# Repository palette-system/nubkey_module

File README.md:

# nubkey_module
Nubkey をPIM447と同じ通信で使用できるようにしたモジュールです。

<br><br>

<table>
<tr><td></td><td></td></tr>
</table>

<br><br>

## ドキュメント

<a href="/docs/structure.md">nubkey_module　基礎知識</a><br>
nubkey_modul を使用するにあたり作成者も、設計者も一度確認してからご使用ください。<br>
<br>

<a href="/docs/module_build.md">nubkey_module　はんだ付け手順</a><br>
nubkey_module をPCBにはんだ付けする際にご確認下さい。<br>
<br>

<a href="/docs/tester_build.md">nubkey_module tester　ビルドガイド</a><br>
nubkey_module tester を組み立てる際にご確認下さい。<br>
<br>

<a href="https://palette-system.github.io/nubkey_module/">nubkey_module tester　ファームウェア書き込み</a><br>
nubkey_module tester を使用する際にご確認下さい。<br>
<br>

<a href="/docs/command.md">nubkey_module　通信仕様</a><br>
nubkey_module で実行できるI2Cのコマンドの仕様書です。QMK等から速度調節する場合等にご確認下さい。<br>
<br>

<a href="/hardware/nubkey_module_tester/">nubkey_module tester　KiCadデータ</a><br>
nubkey_module tester のKiCadデータです。nubkey_module を使用したキーボードを作る際の参考にして下さい。<br>
<br>
<br>

## 基本的な接続
<br>
<br>
<br>

## キャリブレーション
どんなに気を付けて作成しても組み立て毎に磁気スイッチの中心位置が0.数ミリズレが生じます。<br>
キャリブレーションスイッチを押したまま、Nubkeyを押下して上下左右にグリグリ動かす事で nubkey_module のソフト側で中心位置を調節できます。<br>
<br>

## オススメの構造
<br>
<br>
<br>

<br>
<br>

## ピンの説明

|  ピン  |  説明  |
|  ----  |  :---  |
|  UPDI  |  nubkey_module のファームを更新するためのピンです  |
|  addr 0x0B  |  nubkey_module のI2Cアドレスを0x0Bにするピンです。<br>このピンをGNDに接続した状態で起動するとI2Cアドレスが0x0Bになります。  |
|  raw res  |  I2CのレスポンスがデフォルトではPIM447互換ですがこのピンをGNDに接続すると「short X座標, short Y座標, short スイッチの押し込み具合」を返すようになります。  |
|  actuation  |  アクチュエーションポイント設定ピンです。このピンをGNDに接続するとアクチュエーション設定モードに入ります。その後GNDへの接続を切断したタイミングのKS-20のスイッチの高さがアクチュエーションポイントとしてnubkey_moduleに保存されます。  |
|  nubkey off  |  このピンをGNDに接続すると、マウス移動が無しの状態になりスイッチのON/OFFのみが変わるようになります。この時actuationピンで設定したスイッチの高さでON/OFFが切り替わります。  |
|  GND  |  GNDです  |
|  VCC  |  電源です。3.3Vを接続して下さい。  |
|  SCL  |  I2C通信用（SCL）  |
|  SDA  |  I2C通信用（SDA）  |
|  calibration  |  キャリブレーションピンです。このピンをGNDに接続した状態でKS-20のスイッチを押してグリグリすると、Nubkeyの中心位置を調節できます。<br>キャリブレーションの結果は nubkey_module に保存されるので起動のたびキャリブレーションを行う必要はありません。  |

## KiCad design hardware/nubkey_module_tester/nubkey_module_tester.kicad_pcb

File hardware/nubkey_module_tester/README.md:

# NUBKEY_MODULE TESTER
nubkey_module をテストする基板です。
<br><br>

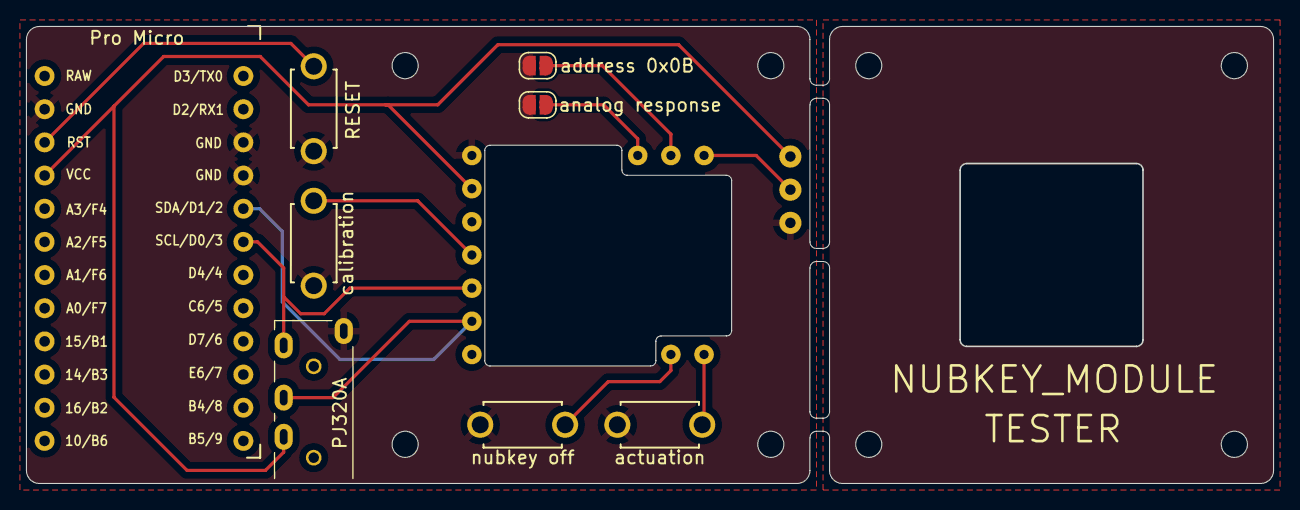
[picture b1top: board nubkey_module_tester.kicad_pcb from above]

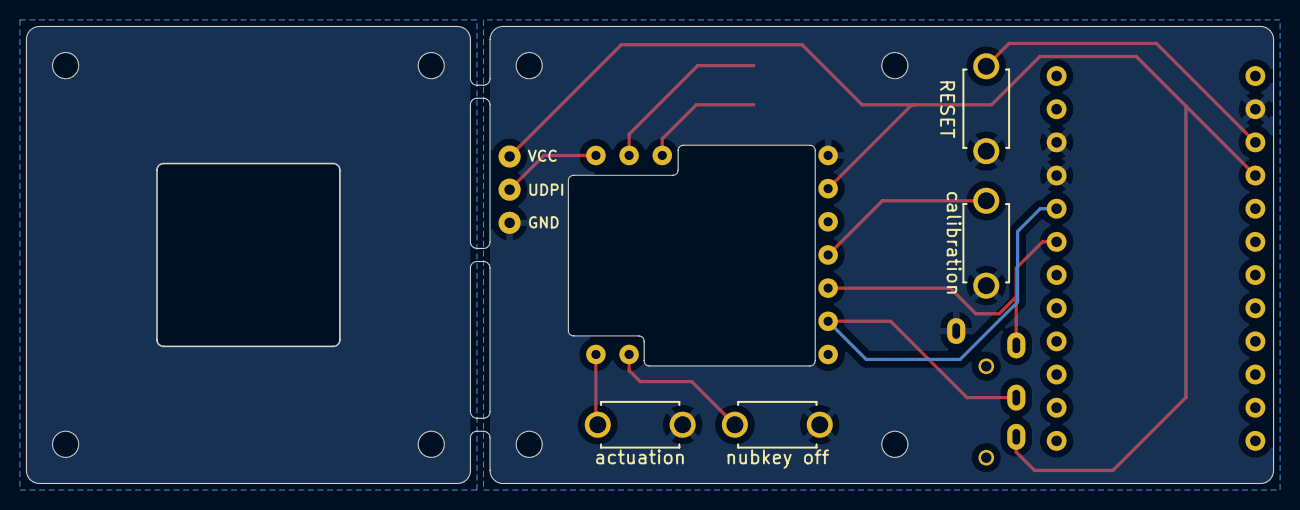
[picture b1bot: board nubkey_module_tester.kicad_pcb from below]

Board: 2 copper layers, 95.5 x 35.0 mm, 11 parts (4 on the bottom side), 11 nets.

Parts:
KEY_HOLE: KEY_HOLE
PJ320A: PJ320A; CON_PJ320A
RESET_SW1: SW_Push; ResetSW
U1: ProMicro; ProMicro_v3
actuation: actuation; ResetSW
address 0x0B: SolderJumper-2_P1.3mm_Open_RoundedPad1.0x1.5mm
analog response: SolderJumper-2_P1.3mm_Open_RoundedPad1.0x1.5mm
calibration: calibration; ResetSW
nubkey off: nubkey off; ResetSW
nubkey_module: nubkey_module
writer: writer; 10pin

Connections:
ADDR: address 0x0B.1, nubkey_module.2
ANA: analog response.1, nubkey_module.3
ATCP: actuation.2, nubkey_module.12
CAL: calibration.2, nubkey_module.7
GND: PJ320A.4, RESET_SW1.1, U1.3, U1.4, U1.23, actuation.1, address 0x0B.2, analog response.2, calibration.1, nubkey off.1, nubkey_module.4, writer.3
NUBOFF: nubkey off.2, nubkey_module.11
RESET: RESET_SW1.2, U1.22
SCL: PJ320A.1, U1.6, nubkey_module.8
SDA: PJ320A.2, U1.5, nubkey_module.9
UDPI: nubkey_module.1, writer.2
VCC: PJ320A.3, U1.21, nubkey_module.5, writer.1

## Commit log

2024-06-01 add new
2024-06-02 module firm update
2024-06-03 add config
2024-06-03 update nub_start_down
2024-06-04 command update
2024-06-08 add docs
2024-06-08 update doc
2024-06-09 add build docs
2024-06-09 add tester build
2024-06-09 update firm
2024-06-14 add web uploader
2024-06-14 move html
2024-06-15 add deploy
2024-06-15 update path
2024-06-15 update build
2024-06-15 update command
2024-06-15 mv yarn.lock
2024-06-15 add parm
2024-06-15 update workflow
2024-06-15 firm up
2024-06-15 update text
2024-06-15 update index
2024-06-15 del await
2024-06-15 add data
2024-06-15 add cast
2024-06-15 add ihex.parse
2024-06-15 cast Buffer
2024-06-15 del file change
2024-06-15 add qmk sorce
2024-06-15 move static
2024-06-15 move data
2024-06-16 complate firm writer
